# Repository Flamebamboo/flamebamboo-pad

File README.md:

# Flamebamboo Pad

## Flamebamboo Studio web app

The macropad editor is in [`web/`](web/README.md). It includes an interactive device layout, custom key and encoder bindings, local profiles, and CircuitPython firmware export.

With Node.js 24 installed:

```bash
cd web
npm ci
npm run dev
```

Open the local address printed by Vite. Profiles are saved in your browser; use **Export to device** to download `code.py` and copy it to your existing CircuitPython/KMK installation. This version does not perform live USB rebinding.

### Features

This is a 11 key macropad with a rotary encoder, an OLED Display that uses KMK firmware (for now)

### Inspirations

Recently I started my content creation journey on the internet where I document my game, app development journey. While I was making this project I decided to make a vlog to document everything from Day 1, making the schematic, pcb, 3D modelling. My content hasn't been consistent but I try my best to post daily. Overall its been 19 days since I started this project back in June 1st (there's some days I didn't work on it).

[Day 2 of building a macropad vlog instagram](https://www.instagram.com/reel/DKhWUYOze7S/)

[Day 2 of building a macropad youtube](https://youtube.com/shorts/7tvncrJ1KWo?si=Fv6e_nwCdUAoQ5EQ)

Feel free to DM me on Slack if you have any feedback or suggestions for improvements! Follow along to see my other content!

## Bill of Materials (BOM)

| Qty | Name                       |
| --- | -------------------------- |
| 12  | 1N4148 diodes              |
| 11  | Cherry MX switches         |
| 1   | 128x32 I2C OLED screen     |
| 1   | EC11 rotary encoder + knob |
| 1   | PCB                        |
| 1   | Seeed Studio XIAO RP2040   |
| 4   | M3x16mm screws             |
| 4   | M3 Heatset                 |
| 11  | Blank DSA white keycaps    |
| 1   | Case top and bottom        |

## CAD Model

## Schematic

## PCB

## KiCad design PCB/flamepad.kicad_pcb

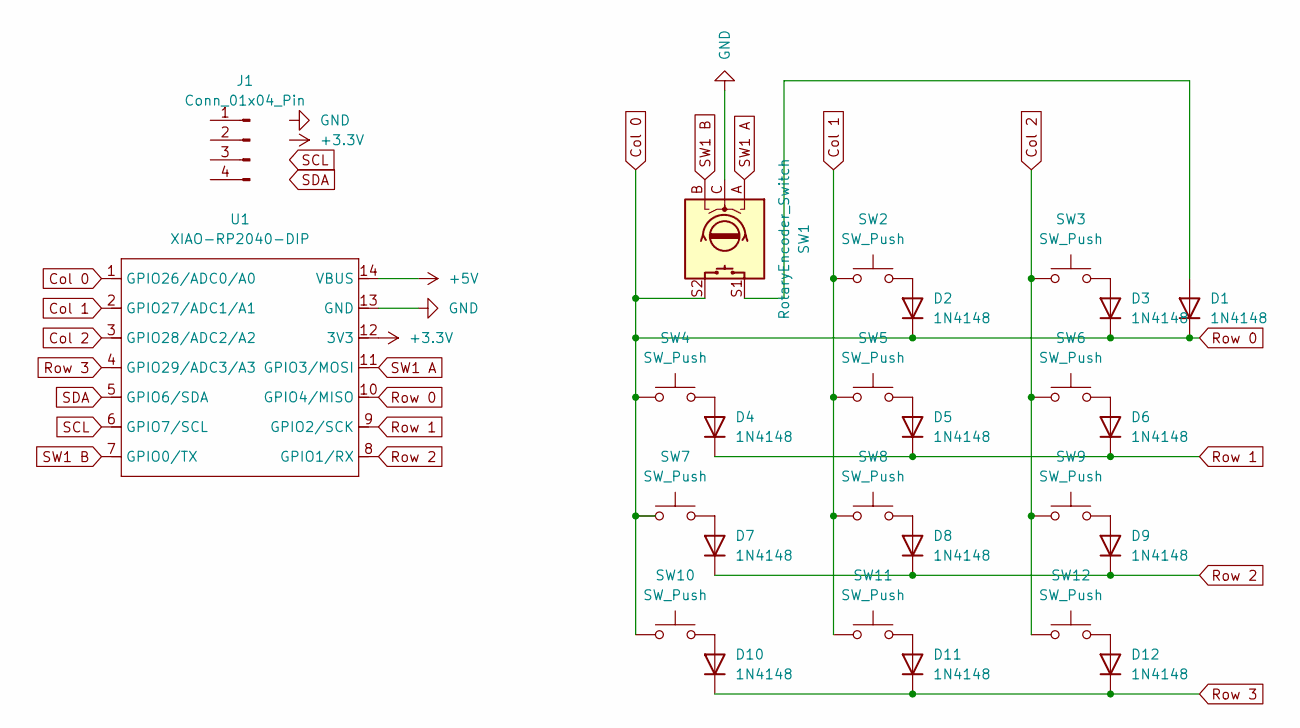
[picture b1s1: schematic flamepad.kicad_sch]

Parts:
D1, D2, D3, D4, D5, D6, D7, D8, D9, D10, D11, D12: 1N4148; D_DO-35_SOD27_P7.62mm_Horizontal
J1: Conn_01x04_Pin; SSD1306-0.91-OLED-4pin-128x32
SW1: RotaryEncoder_Switch; RotaryEncoder_Alps_EC11E-Switch_Vertical_H20mm
SW2, SW3, SW4, SW5, SW6, SW7, SW8, SW9, SW10, SW11, SW12: SW_Push; SW_Cherry_MX_1.00u_PCB
U1: XIAO-RP2040-DIP

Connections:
+3.3V: J1.2, U1.12 (3V3)
+5V: U1.14 (VBUS)
Col 0: D1.1 (K), D2.1 (K), D3.1 (K), SW1.S2, SW4.1, SW7.1, SW10.1, U1.1 (GPIO26/ADC0/A0), U1.10 (GPIO4/MISO)
Col 1: SW2.1, SW5.1, SW8.1, SW11.1, U1.2 (GPIO27/ADC1/A1)
Col 2: SW3.1, SW6.1, SW9.1, SW12.1, U1.3 (GPIO28/ADC2/A2)
GND: J1.1, SW1.C, U1.13 (GND)
unnamed: D1.2 (A), SW1.S1
unnamed: D2.2 (A), SW2.2
unnamed: D3.2 (A), SW3.2
unnamed: D4.2 (A), SW4.2
unnamed: D5.2 (A), SW5.2
unnamed: D6.2 (A), SW6.2
unnamed: D7.2 (A), SW7.2
unnamed: D8.2 (A), SW8.2
unnamed: D9.2 (A), SW9.2
unnamed: D10.2 (A), SW10.2
unnamed: D11.2 (A), SW11.2
unnamed: D12.2 (A), SW12.2
Row 1: D4.1 (K), D5.1 (K), D6.1 (K), U1.9 (GPIO2/SCK)
Row 2: D7.1 (K), D8.1 (K), D9.1 (K), U1.8 (GPIO1/RX)
Row 3: D10.1 (K), D11.1 (K), D12.1 (K), U1.4 (GPIO29/ADC3/A3)
SCL: J1.3, U1.6 (GPIO7/SCL)
SDA: J1.4, U1.5 (GPIO6/SDA)
SW1 A: SW1.A, U1.11 (GPIO3/MOSI)
SW1 B: SW1.B, U1.7 (GPIO0/TX)

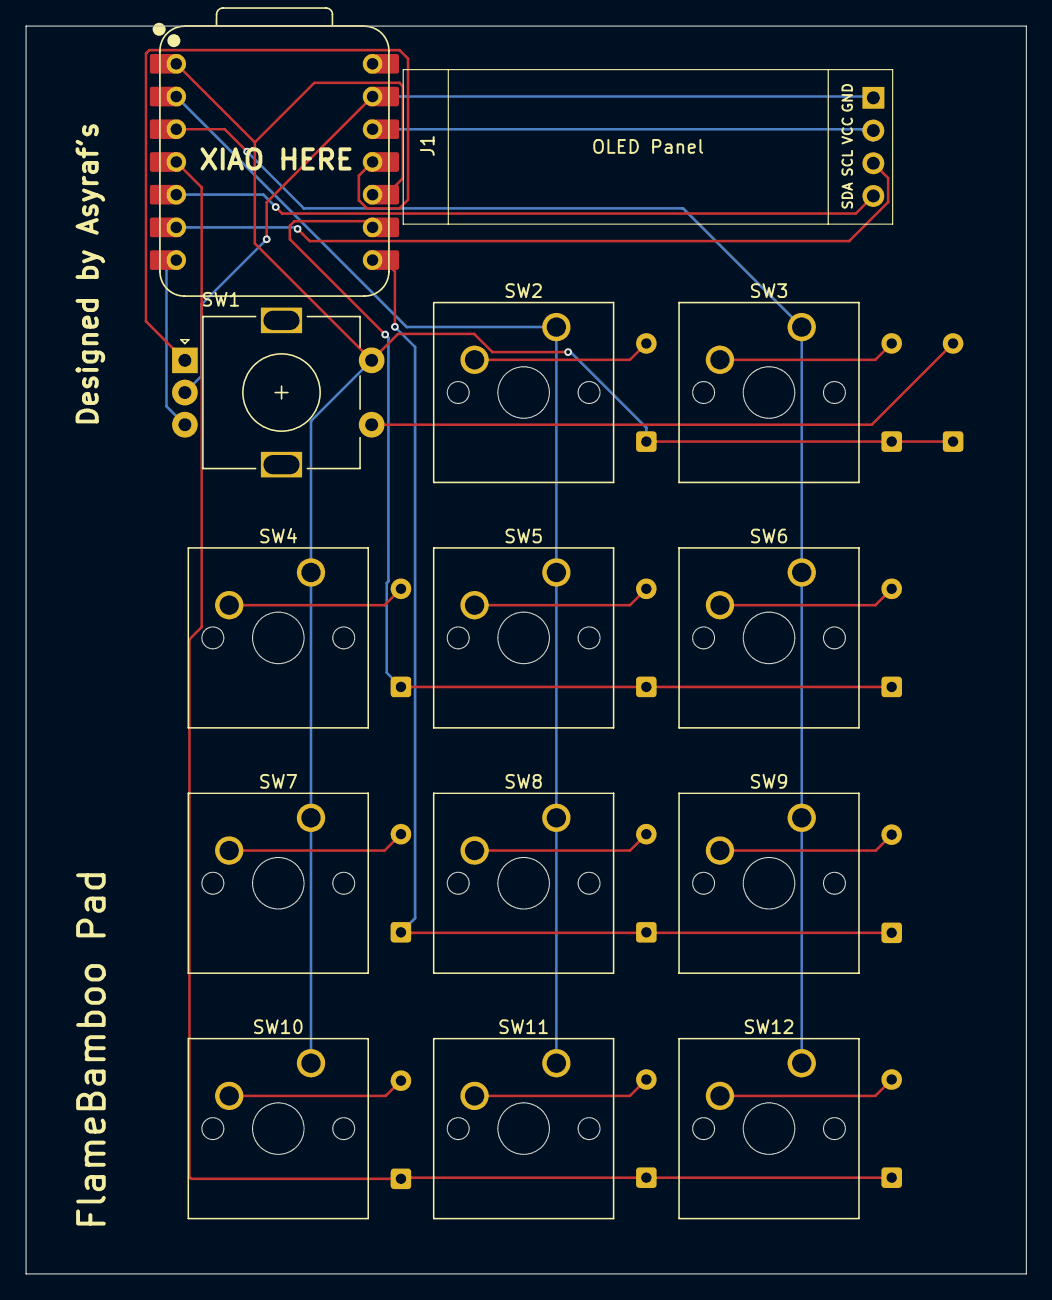
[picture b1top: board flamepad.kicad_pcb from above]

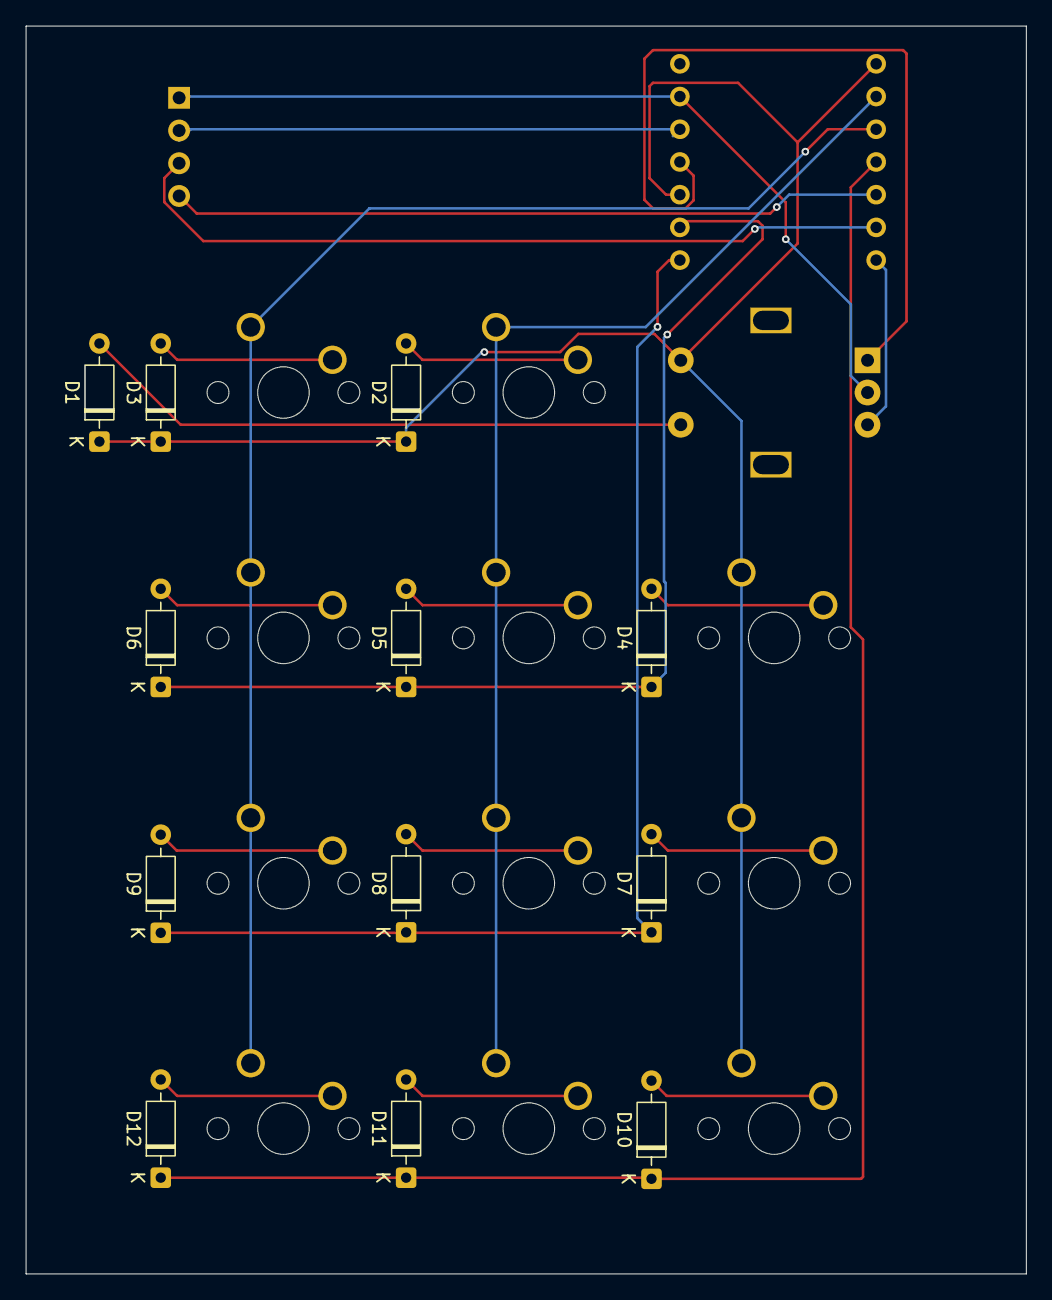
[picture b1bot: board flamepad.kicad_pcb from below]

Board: 2 copper layers, 77.7 x 96.9 mm, 26 parts (12 on the bottom side), 24 nets.

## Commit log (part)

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2025-06-19 meet all requirements
2025-06-30 prodfil Gerber update due to mislook mistake in DRC check.
2025-07-16 Correcting the pins NO
2025-07-18 customised for video editing
